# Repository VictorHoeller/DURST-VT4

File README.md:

# DURST-VT4
It is a tap tempo pedal with which you can synchronize and start external MIDI devices, such as beat machines and other sequencers. Furthermore, external effect pedals with tap input can also be synchronized to the same speed. Mostly these are delay (DOD Rubberneck) or modulation pedals.
The pedal acts as a MIDI master clock.

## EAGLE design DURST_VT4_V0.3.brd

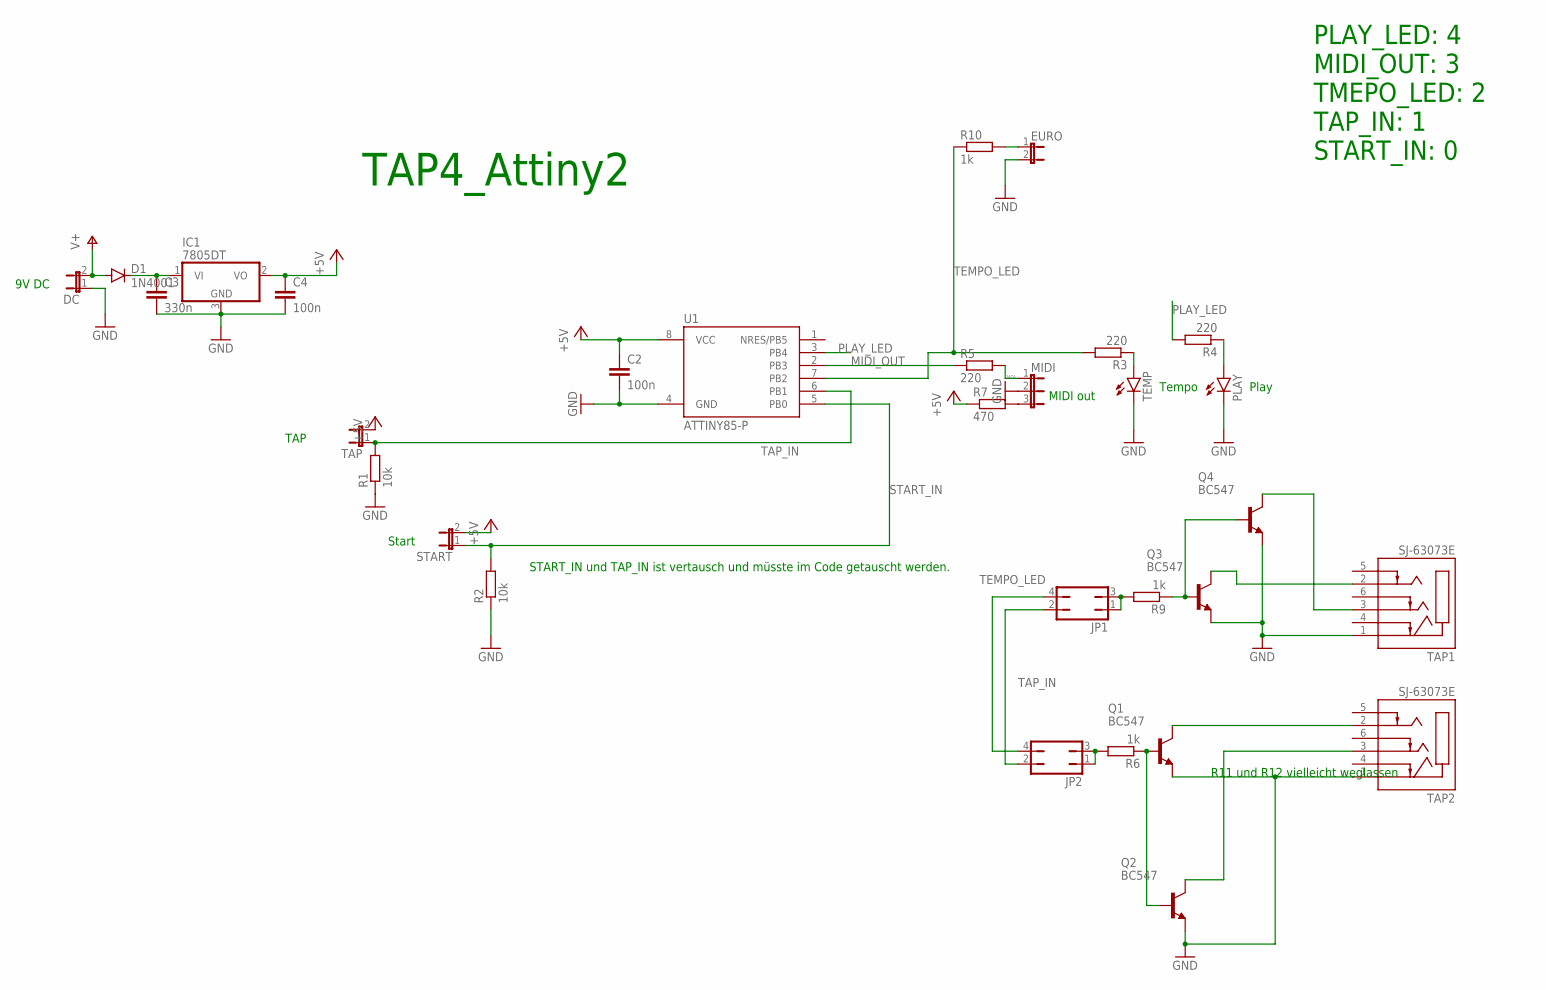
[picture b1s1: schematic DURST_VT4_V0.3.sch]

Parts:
C2: 100n; C050-024X044
C3: 330n; C025-024X044
C4: 100n; C025-024X044
D1: 1N4001; DO41-10
DC: JP1E; JP1
EURO: JP1E; JP1
IC1: 7805DT; TO252
JP1, JP2: JP2Q
MIDI: JP2E; JP2
PLAY: LED5MM
Q1, Q2, Q3, Q4: BC547; TO92
R1, R2: 10k; 0309/10
R3, R4, R5: 220; 0309/10
R6, R9, R10: 1k; 0309/10
R7: 470; 0309/10
START: JP1E; JP1
TAP: JP1E; JP1
TAP1, TAP2: SJ-63073E; CUI_SJ-63073E
TEMP: LED5MM
U1: ATTINY85-P; PDIP08_300MIL

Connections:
+5V: C2.1, C4.1, IC1.2 (VO), R7.1, START.2, TAP.2, U1.8 (VCC)
DATA: MIDI.1, R5.2
GND: C2.2, C3.2, C4.2, DC.1, EURO.2, IC1.3 (GND), MIDI.2, PLAY.K (C), Q1.1 (E), Q2.1 (E), Q3.1 (E), Q4.1 (E), R1.1, R2.1, TAP1.1 (SLEEVE), TAP2.1 (SLEEVE), TEMP.K (C), U1.4 (GND)
MIDI_OUT: R5.1, U1.2 (PB3)
unnamed: EURO.1, R10.2
unnamed: Q4.3 (C), TAP1.3 (RING)
unnamed: Q2.3 (C), TAP2.3 (RING)
unnamed: R3.1, TEMP.A
unnamed: PLAY.A, R4.1
unnamed: JP1.1, JP1.3, R9.2
unnamed: C3.1, D1.C, IC1.1 (VI)
unnamed: JP2.1, JP2.3, R6.2
unnamed: MIDI.3, R7.2
unnamed: Q3.3 (C), TAP1.2 (TIP)
unnamed: Q1.3 (C), TAP2.2 (TIP)
unnamed: Q1.2 (B), Q2.2 (B), R6.1
unnamed: Q3.2 (B), Q4.2 (B), R9.1
PLAY_LED: R4.2, U1.3 (PB4)
START_IN: R2.2, START.1, U1.5 (PB0)
TAP_IN: JP1.2, JP2.2, R1.2, TAP.1, U1.6 (PB1)
TEMPO_LED: JP1.4, JP2.4, R3.2, R10.1, U1.7 (PB2)
V+: D1.A, DC.2

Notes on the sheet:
9V DC
TAP
Start
Tempo
Play
MIDI out
TAP4_Attiny2
R11 und R12 vielleicht weglassen
START_IN und TAP_IN ist vertausch und müsste im Code getauscht werden.
PLAY_LED: 4 MIDI_OUT: 3 TMEPO_LED: 2 TAP_IN: 1 START_IN: 0

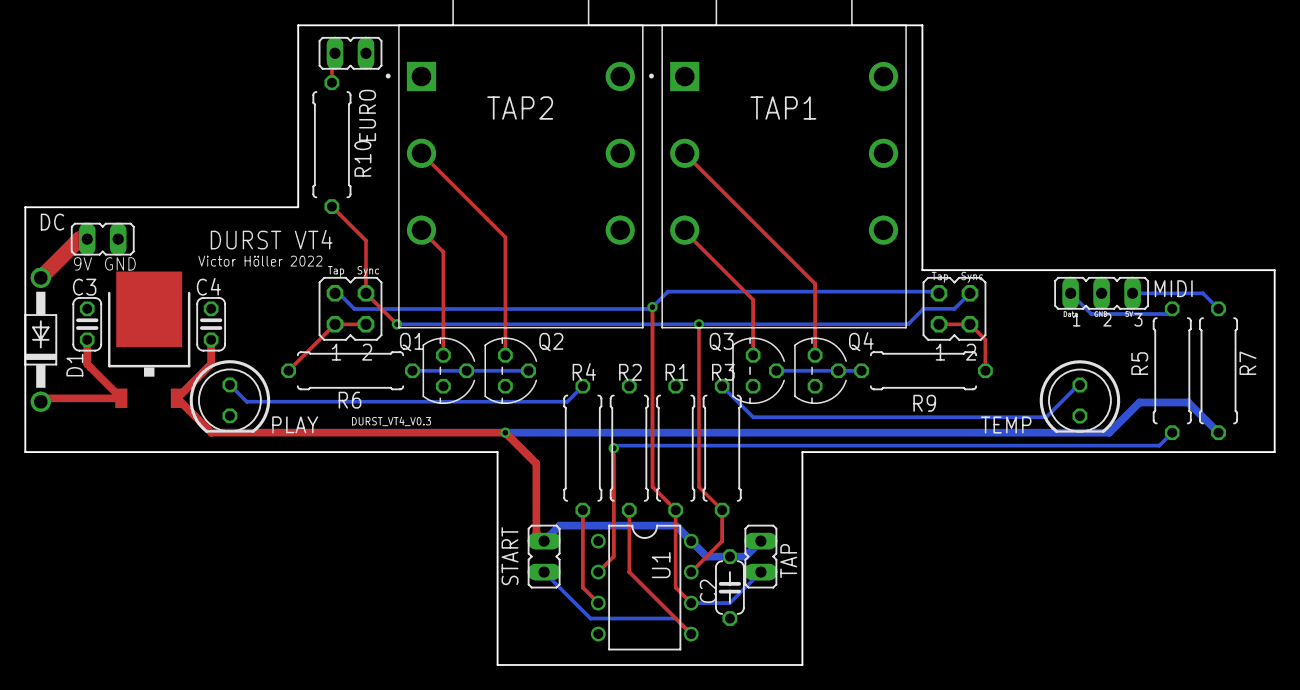
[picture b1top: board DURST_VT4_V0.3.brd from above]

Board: 2 copper layers, 102.5 x 52.5 mm, 30 parts (0 on the bottom side), 22 nets.

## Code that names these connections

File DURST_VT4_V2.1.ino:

// written by Victor Höller 2022
// V2.1
// fits for Board: DURST_VT4_V0.3
// use TimerOne.h from this side: https://github.com/PaulStoffregen/TimerOne
// replace the TimerOne folder C:\Users\Victor Höller\Documents\Arduino\libraries

//NEU: Zeile 66, 104

#include <TimerOne.h>
#include <EEPROM.h>
#include <Bounce2.h>
#include <SendOnlySoftwareSerial.h>
SendOnlySoftwareSerial midiSerial(3);

#define START_IN 0
#define TAP_IN 1
#define TEMPO_LED 2
#define PLAY_LED 4

#define BLINK_TIME 5

#define MIDI_START 0xFA
#define MIDI_STOP 0xFC

#define MIDI_TIMING_CLOCK 0xF8
#define CLOCKS_PER_BEAT 24

// BPM Variablen
Bounce A = Bounce();
Bounce B = Bounce();
float bpm = EEPROM.read(0);
float bpm_dec = EEPROM.read(1);
byte anzahl_press = 0;
long last_tap;
long now;
bool saved = true;

float bpm4;
float bpm3;
float bpm2;
float bpm1;
float bpm0;

// Algemeine Variablen
volatile int blinkCount = 0;

// Midi Variablen
long intervalMicroSeconds;
boolean playing = false;

void setup() {
  midiSerial.begin(31250);
  pinMode(TEMPO_LED, OUTPUT);
  pinMode(PLAY_LED, OUTPUT);

  // Attach the interrupt to send the MIDI clock and start the timer
  Timer1.initialize(intervalMicroSeconds);
  Timer1.setPeriod(calculateIntervalMicroSecs(bpm));
  Timer1.attachInterrupt(sendClockPulse);

  A.attach(TAP_IN, INPUT);
  A.interval(25);
  B.attach(START_IN, INPUT);
  B.interval(25);

  // bpm = bpm + bpm_dec/100;
}

void loop() {
  // Prozedur, wenn Tap gedrückt und debouncen des Tasters
  A.update();
  now = millis();  // Aktuelle Zeit in Millisekunden
  if (A.rose()) {
    anzahl_press++;               // erhöht den Wert der Tasthäufigkeit um 1
    if (anzahl_press > 1) {
      bpm4 = 60000 / float(now - last_tap);
      if (anzahl_press == 2) {
        bpm0 = bpm4;
        bpm1 = bpm4;
        bpm2 = bpm4;
        bpm3 = bpm4;
      }
      else {
        bpm0 = bpm1;
        bpm1 = bpm2;
        bpm2 = bpm3;
        bpm3 = bpm4;
      }
      bpm = (bpm4 + bpm3 + bpm2 + bpm1 + bpm0) / 5;
      Timer1.setPeriod(calculateIntervalMicroSecs(bpm));
      saved = false;
    }
    last_tap = now;
  }

  // Schaut, ob eine NEUE Sequenz begonnen werden soll
  if (now - last_tap > 2000) {  // nach 2 Sekunden gehört ein Tap nicht mehr zu der alten Sequenz und eine neue wird begonnen
    anzahl_press = 0;           // Anzahl Pressungen wird auf Null gesetzt.
    if (saved == false) {
      if (bpm > 255) {
        bpm = 255;
      }
      EEPROM.write(0, byte(bpm));
      //EEPROM.write(1, byte((bpm - byte(bpm) * 100)));
      saved = true;
    }
  }

  B.update();
  // Schaut, ob Startknopf gedrückt wurde
  if (B.fell()) {
    startOrStop();
  }
}
